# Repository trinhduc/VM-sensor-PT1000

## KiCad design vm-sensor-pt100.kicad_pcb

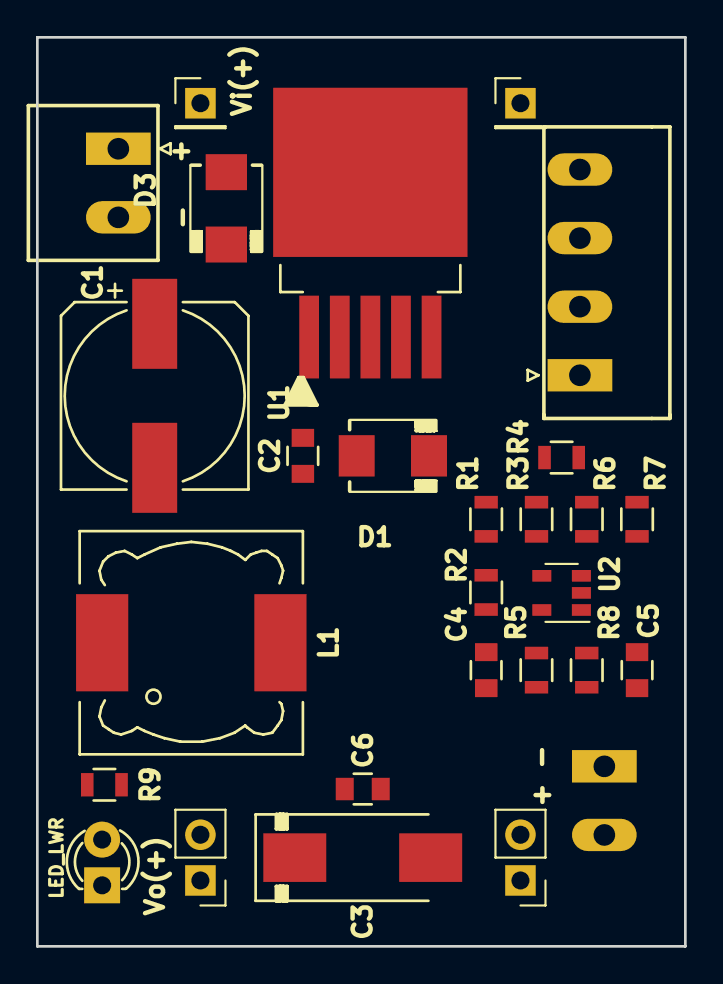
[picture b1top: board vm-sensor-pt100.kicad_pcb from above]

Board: 2 copper layers, 36.0 x 50.5 mm, 28 parts (1 on the bottom side), 12 nets, no tracks yet.

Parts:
C1: 470uF/50v; c_elec_10x10.5
C2: 10uF/50v; C_0805
C3: 330uF/16V; Tantalum_Case-D_EIA-7343-31_Hand
C4, C5: 10uF; C_0805
C6: 10uF/16v; C_0805
D1, D3: SS34; do214aa-g
D2: LED_PWR; LED-3MM
L1: 47uH/RH127-470; Choke_SMD_12x12mm_h8mm
P1: Vin; Pluggable-Terminal-Block-2P-3.81pitch.pretty
P2: Vin(+); Pin_Header_Straight_1x01_Pitch2.54mm
P3: PT100; Domino-PT100.pretty
P4: ADC; Pluggable-Terminal-Block-2P-3.81pitch.pretty
P5: Vo(+); Pin_Header_Straight_1x02_Pitch2.54mm
P6: Vo(-); Pin_Header_Straight_1x02_Pitch2.54mm
P7: Vin(-); Pin_Header_Straight_1x01_Pitch2.54mm
R1, R4: 3.3K/1%; R_0805
R2: 100R/1%; R_0805
R3, R6: 16.9K/1%; R_0805
R5, R7: 1M/1%; R_0805
R8: 1K/1%; R_0805
R9: 100R; R_0805
U1: LM2596S-3.3; TO-263-5Lead
U2: MCP601T; SOT-23-5

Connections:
+3V3: C3.1, C4.1, C6.1, L1.2, P5.1, P5.2, R1.1, R4.1, R9.1, U1.4, U2.5
/ADC: C5.1, P4.1, R8.1
/Blue: P3.3, P3.4, R4.2, R6.2
GND: C1.2, C2.2, C3.2, C4.2, C5.2, C6.2, D1.2, D2.1, P1.2, P3.1, P3.2, P4.2, P6.1, P6.2, P7.1, R2.2, R7.1, U1.3, U1.5, U2.2
unnamed: C1.1, C2.1, D3.1, U1.1
unnamed: D1.1, L1.1, U1.2
unnamed: D2.2, R9.2
unnamed: R1.2, R2.1, R3.2
unnamed: R3.1, R5.1, U2.4
unnamed: R5.2, R8.2, U2.1
unnamed: R6.1, R7.2, U2.3
VCC: D3.2, P1.1, P2.1

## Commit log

2017-01-14 fix BIG MISTAKE-change LM2595S-3.3 to LM2596S-3.3
2017-01-14 Completed Fix PCB
2017-01-18 add diode D3-SS34 in Vin & modifu footprint header ADC & PWR
2017-01-18 fix footprint Pluggable-Terminal-Block-2P-3.81pitch
2017-01-18 setup PCB completed
